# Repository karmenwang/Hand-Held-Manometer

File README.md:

# Hand-Held-Manometer
Utilizes DLHR Module to detect differential pressure

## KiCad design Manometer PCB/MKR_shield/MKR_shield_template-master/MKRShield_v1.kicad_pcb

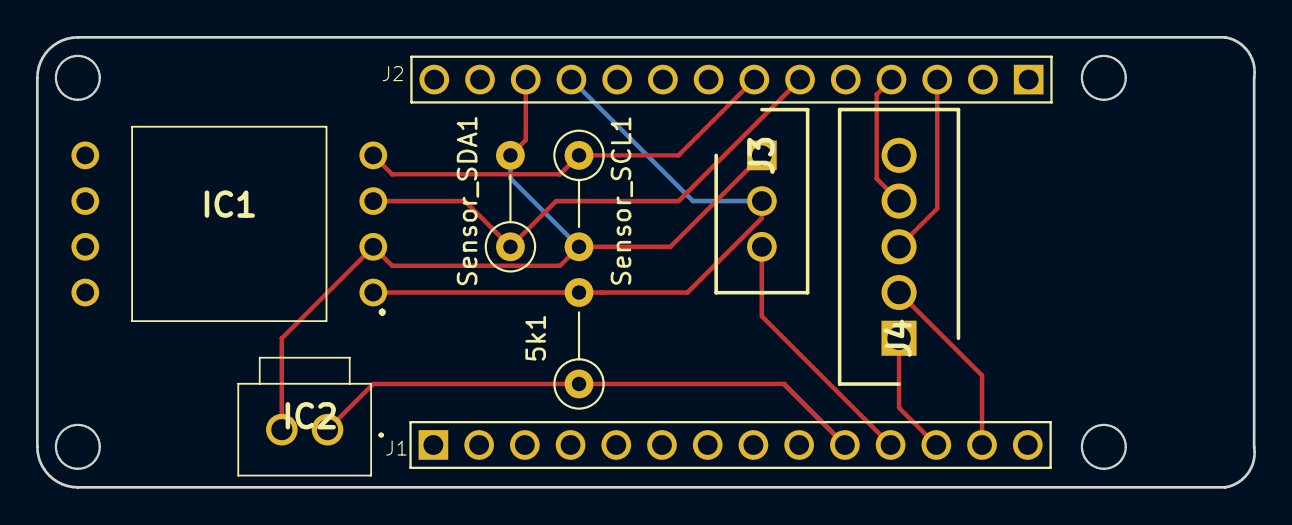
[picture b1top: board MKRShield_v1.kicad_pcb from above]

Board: 4 copper layers, 67.6 x 25.0 mm, 18 parts (0 on the bottom side), 10 nets.

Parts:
5k1: Button_Resistor; R_Axial_DIN0207_L6.3mm_D2.5mm_P5.08mm_Vertical
@HOLE0, @HOLE1, @HOLE2, @HOLE3: (no value)
FRAME1: Page 1; FRAME
IC1: DLHR-L10D-E1BD-C-NAV8; DLHRL10DE1BDCNAV8
IC2: 171971-0102; 1719710102
J1, J2: 61301411121
J3: 70543-0037; SHDR3W89P0X254_1X3_1017X508X1143P
J4: 70543-0004; SHDR5W109P0X254_1X5_1525X660X1143P
Sensor_SCL1: 1k; R_Axial_DIN0207_L6.3mm_D2.5mm_P5.08mm_Vertical
Sensor_SDA1: 1k; R_Axial_DIN0207_L6.3mm_D2.5mm_P5.08mm_Vertical
U$5, U$6, U$7, U$8: MH_RND_F_2.2MM_NM

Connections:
GND: 5k1.2, IC1.1, J2.11, J3.2
unnamed: 5k1.1, IC2.1, J1.10
unnamed: IC1.2, IC2.2, J2.12, J3.1, Sensor_SCL1.2, Sensor_SDA1.2
unnamed: IC1.3, J2.6, Sensor_SDA1.1
unnamed: IC1.4, J2.7, Sensor_SCL1.1
unnamed: J1.11, J3.3
unnamed: J1.12, J4.1
unnamed: J1.13, J4.2
unnamed: J2.3, J4.3
unnamed: J2.4, J4.4

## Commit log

2020-12-21 updated Manometer Enclosure STL files
